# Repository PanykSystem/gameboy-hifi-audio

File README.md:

# GameBoy HiFi Audio

A Bluetooth audio upgrade for the Game Boy Advance. It removes the console's
stock audio amp and replaces the whole audio back end with an ESP32 and an
ES8388 codec. The mod streams game audio to Bluetooth headphones and speakers,
and it also drives the GBA's built-in speaker and wired headphone jack itself,
with onboard EQ, volume, and sound effects.

<p align="center">
  
  <br>
  <sub>What the mod does, start to finish</sub>
</p>

<p align="center">
  
  &nbsp;&nbsp;
  
  <br>
  <sub>AGB main board (left) and flex (right)</sub>
</p>

What you get:

- Bluetooth (A2DP) output to any standard headphones or speaker.
- Wired headphones and the internal speaker, driven by the onboard codec.
- EQ, volume, and sound-effect cues, tunable from a phone or laptop over
  Bluetooth (no app install, it runs in the browser).
- A battery-saver mode that puts the radio and CPU to sleep and passes audio
  through the codec in analog, for long unplugged sessions.
- Firmware updates over Bluetooth.

<p align="center">
  
  <br>
  <sub>The browser config page: a live spectrum and per-output EQ, tuned over Bluetooth with no app to install</sub>
</p>

Prebuilt, pre-assembled kits are coming soon at
[cajunpanda.com](https://cajunpanda.com/shop/gameboy-hifi-audio), for anyone who would
rather not source the parts and solder it themselves. Kits ship pre-flashed and update
over Bluetooth, so they need no programming cable. The listing also has an A/B recording
of the mod with its filters off and on, and an optional speaker.

Questions, build photos, and troubleshooting happen on the
[Discord](https://discord.gg/6BNetnK6kC).

This repository currently holds the board for the original Game Boy Advance
(AGB). The firmware is shared across models. Boards for other Game Boy models
will be added under `hardware/` as they are designed.

## Pick your path

This project has three kinds of reader. Start with the doc that matches you.

- **You have a GameBoy HiFi board, or one already in your GBA.**
  [docs/AGB-INSTALL.md](docs/AGB-INSTALL.md) fits the board into a Game Boy Advance, and
  [docs/MANUAL.md](docs/MANUAL.md) covers using it: pairing, the control button,
  the modes, the web config page, and troubleshooting.

- **You want to build the boards yourself.**
  Read [docs/HARDWARE.md](docs/HARDWARE.md): the bill of materials, the KiCad
  boards, fabrication, and assembly. It links on to the install guide once the
  boards are ready.

- **You want to change the firmware.**
  Read [docs/FIRMWARE.md](docs/FIRMWARE.md): the toolchain, build and flash,
  the architecture, the config options, and how the control surfaces work.

## Repository layout

```
firmware/        ESP-IDF firmware (PlatformIO project), shared across boards
hardware/agb/    KiCad projects for the AGB main board and flex (schematic carries the BOM)
web/             Web Bluetooth config page (hosted on GitHub Pages)
tools/           make_clip.py (clip authoring), bringup.py (bench current<->boot correlation)
docs/            the guides above
```

## License

- Firmware and other source code: MIT, see [LICENSE](LICENSE).
- Hardware (schematics, board layouts, footprints): CERN-OHL-P v2, see
  [hardware/LICENSE](hardware/LICENSE).
- Documentation: CC BY 4.0, see [docs/LICENSE](docs/LICENSE).

You can build, modify, sell, and redistribute all of it, including in your own
products, as long as you keep the attribution and the license notices.

## A note on the trademark

Game Boy and Game Boy Advance are trademarks of Nintendo. This is an
independent, unofficial project and is not affiliated with or endorsed by
Nintendo.

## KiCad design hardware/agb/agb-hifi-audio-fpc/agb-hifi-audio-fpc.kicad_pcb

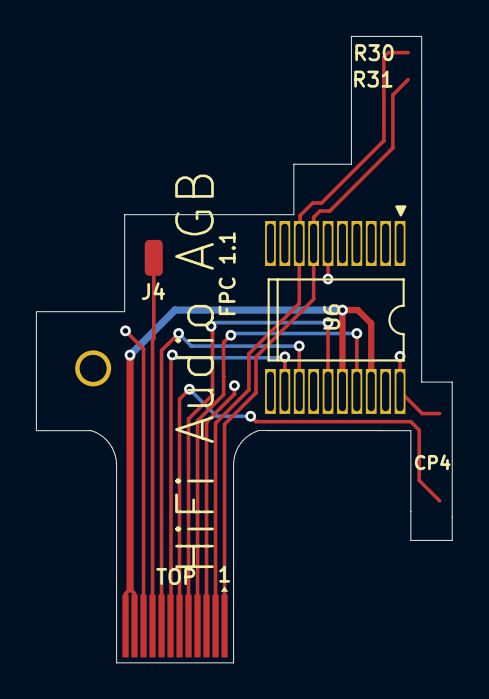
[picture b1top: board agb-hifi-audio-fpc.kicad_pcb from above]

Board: 2 copper layers, 23.1 x 34.8 mm, 3 parts (0 on the bottom side), 9 nets.

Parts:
J1: AGB_AMP_CONNECT; AGB AMP CONNECT
J4: PAIR; SolderWirePad_1x01_SMD_1x2mm
J5: BOARD_CONNECT; FPC-Tail-12pos-0.5mm-FH12A

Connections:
GND: J1.6, J1.18, J5.3, J5.10
LIN: J1.8, J5.2
LOUT: J1.13, J5.5
PAIR: J4.1 (Pin_1_1), J5.9
RIN: J1.7, J5.1
ROUT: J1.15, J5.4
SW: J1.11, J5.8
VBAT: J1.14, J1.16, J5.11, J5.12
VOL: J1.10, J5.7
